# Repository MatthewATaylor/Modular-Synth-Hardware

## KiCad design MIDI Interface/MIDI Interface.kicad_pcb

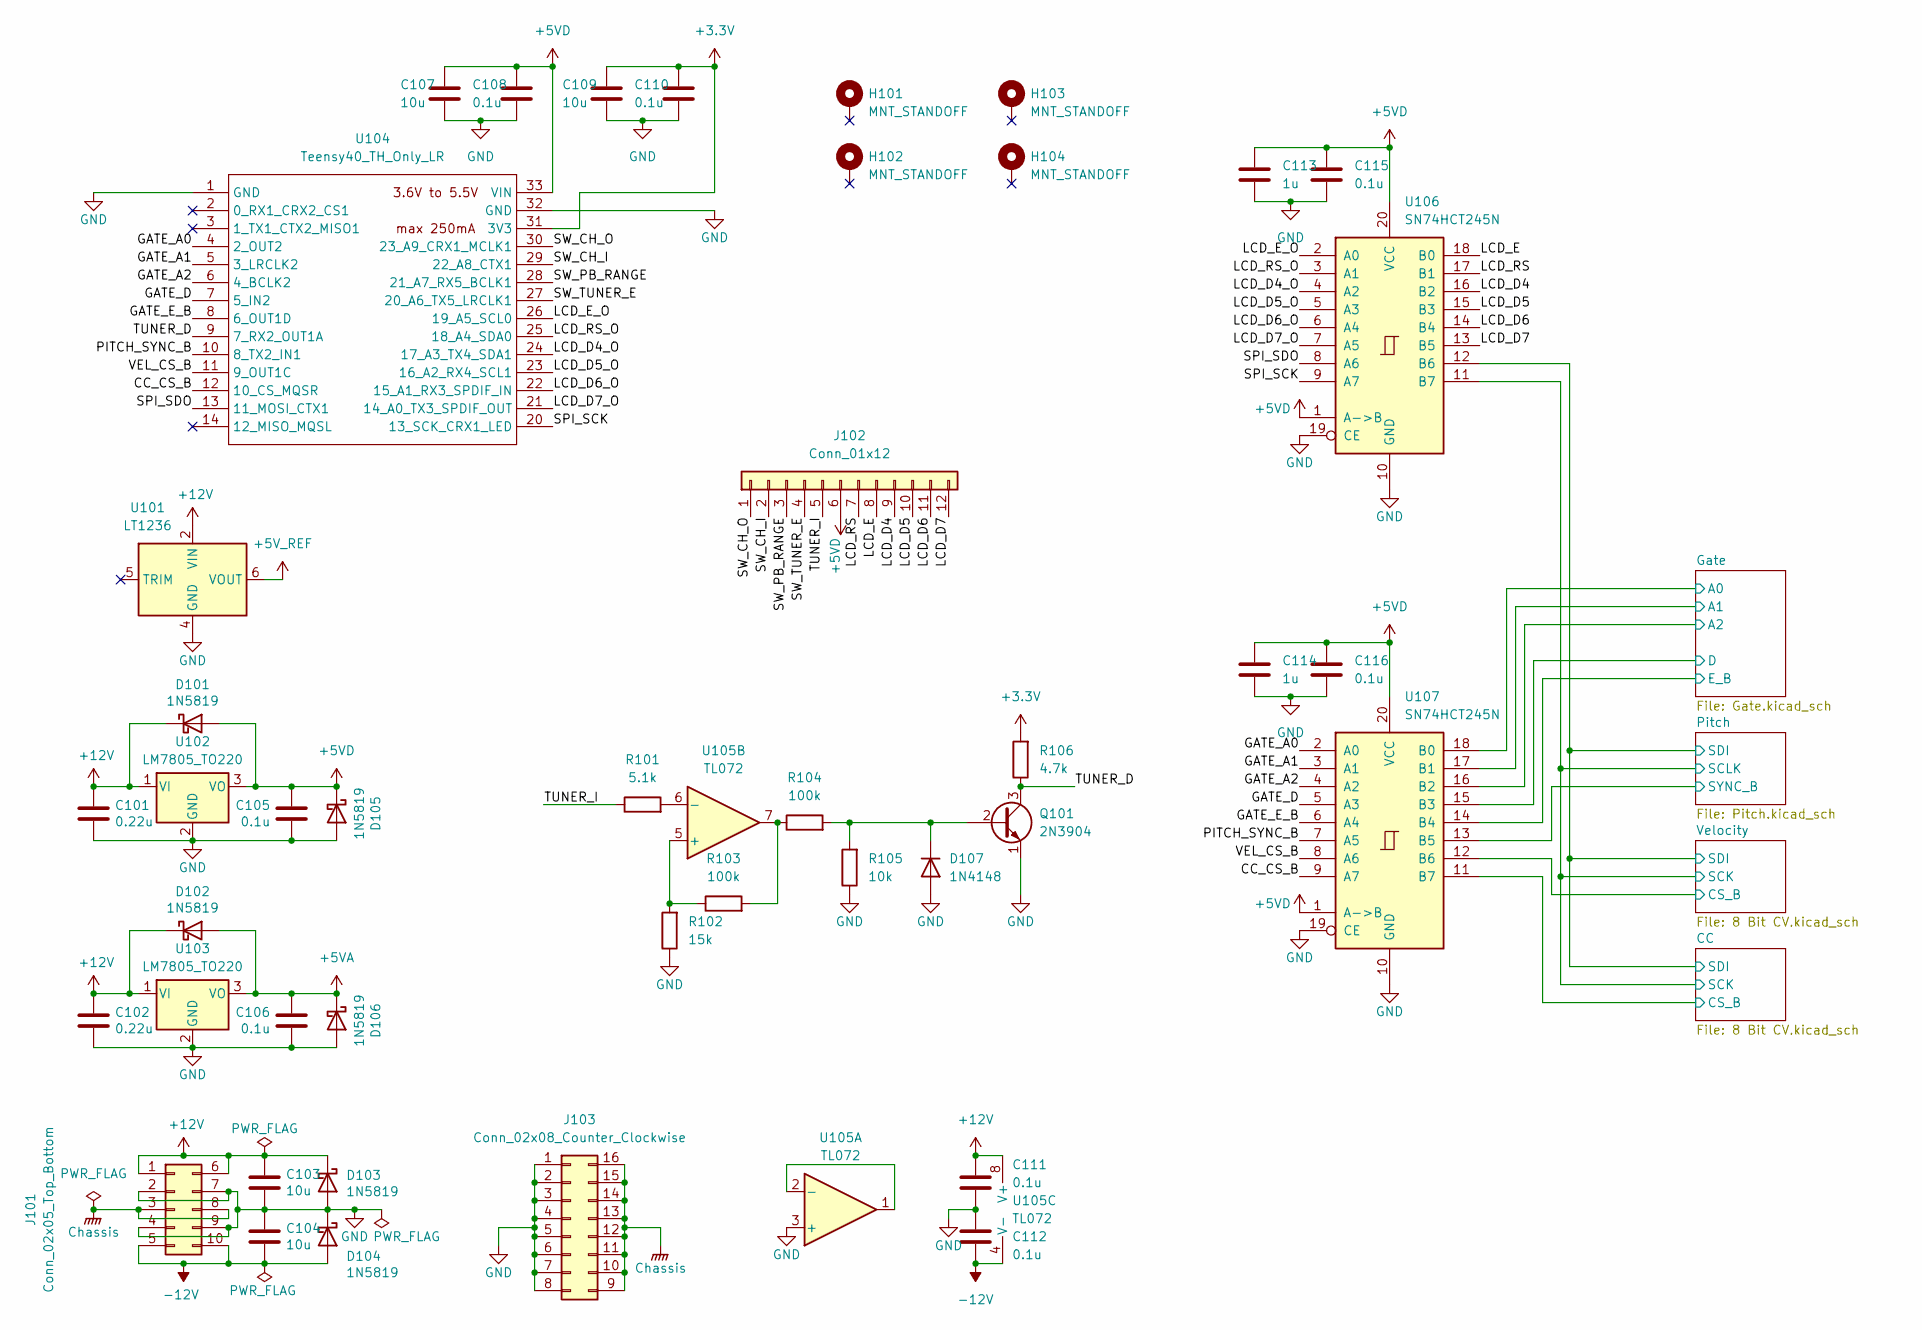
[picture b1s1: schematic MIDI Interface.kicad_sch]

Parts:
C101, C102: 0.22u; C_Disc_D5.5mm_W2.5mm_P2.50mm
C103, C104, C107, C109: 10u; C_Disc_D5.5mm_W4.0mm_P2.50mm
C105, C106, C108, C110, C111, C112, C115, C116: 0.1u; C_Disc_D5.5mm_W2.5mm_P2.50mm
C113, C114: 1u; C_Disc_D5.5mm_W4.0mm_P2.50mm
D101, D102, D103, D104, D105, D106: 1N5819; D_DO-41_SOD81_P10.16mm_Horizontal
D107: 1N4148; D_DO-35_SOD27_P7.62mm_Horizontal
H101, H102, H103, H104: MNT_STANDOFF; MountingHole_Pitch7.5mm_Drill3.4mm
J101: Conn_02x05_Top_Bottom; Molex_Mini-Fit_Jr_5566-10A_2x05_P4.20mm_Vertical
J102: Conn_01x12; PinSocket_1x12_P2.54mm_Vertical
J103: Conn_02x08_Counter_Clockwise; PinSocket_2x08_P2.54mm_Vertical
Q101: 2N3904; TO-92_HandSolder
R101: 5.1k; R_Axial_DIN0207_L6.3mm_D2.5mm_P7.62mm_Horizontal
R102: 15k; R_Axial_DIN0207_L6.3mm_D2.5mm_P7.62mm_Horizontal
R103, R104: 100k; R_Axial_DIN0207_L6.3mm_D2.5mm_P7.62mm_Horizontal
R105: 10k; R_Axial_DIN0207_L6.3mm_D2.5mm_P7.62mm_Horizontal
R106: 4.7k; R_Axial_DIN0207_L6.3mm_D2.5mm_P7.62mm_Horizontal
U101: LT1236; DIP-8_W7.62mm_Socket
U102, U103: LM7805_TO220; TO-220-3_Vertical
U104: Teensy40_TH_Only_LR
U105: TL072; DIP-8_W7.62mm_Socket
U106, U107: SN74HCT245N; DIP-20_W7.62mm_Socket

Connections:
+3.3V: C109.1, C110.1, R106.2, U104.31 (3V3)
+5VA: C106.1, D102.2 (A), D106.1 (K), U103.3 (VO); also elsewhere on the board
+5VD: C105.1, C107.1, C108.1, C113.1, C114.1, C115.1, C116.1, D101.2 (A), D105.1 (K), J102.6, U102.3 (VO), U104.33 (VIN), U106.1 (A->B), U106.20 (VCC), U107.1 (A->B), U107.20 (VCC); also elsewhere on the board
+5V_REF: U101.6 (VOUT); also elsewhere on the board
+12V: C101.1, C102.1, C103.1, C111.2, D101.1 (K), D102.1 (K), D103.1 (K), J101.1, J101.6, U101.2 (VIN), U102.1 (VI), U103.1 (VI), U105.8 (V+); also elsewhere on the board
-12V: C104.2, C112.1, D104.2 (A), J101.5, J101.10, U105.4 (V-); also elsewhere on the board
/CC/CS_B: U107.11 (B7); also elsewhere on the board
/CC/SCK: U106.11 (B7); also elsewhere on the board
/CC/SDI: U106.12 (B6); also elsewhere on the board
/CC_CS_B: U104.12 (10_CS_MQSR), U107.9 (A7)
/GATE_A0: U104.4 (2_OUT2), U107.2 (A0)
/GATE_A1: U104.5 (3_LRCLK2), U107.3 (A1)
/GATE_A2: U104.6 (4_BCLK2), U107.4 (A2)
/GATE_D: U104.7 (5_IN2), U107.5 (A3)
/GATE_E_B: U104.8 (6_OUT1D), U107.6 (A4)
/Gate/A0: U107.18 (B0); also elsewhere on the board
/Gate/A1: U107.17 (B1); also elsewhere on the board
/Gate/A2: U107.16 (B2); also elsewhere on the board
/Gate/D: U107.15 (B3); also elsewhere on the board
/Gate/E_B: U107.14 (B4); also elsewhere on the board
/LCD_D4: J102.9, U106.16 (B2)
/LCD_D4_O: U104.24 (17_A3_TX4_SDA1), U106.4 (A2)
/LCD_D5: J102.10, U106.15 (B3)
/LCD_D5_O: U104.23 (16_A2_RX4_SCL1), U106.5 (A3)
/LCD_D6: J102.11, U106.14 (B4)
/LCD_D6_O: U104.22 (15_A1_RX3_SPDIF_IN), U106.6 (A4)
/LCD_D7: J102.12, U106.13 (B5)
/LCD_D7_O: U104.21 (14_A0_TX3_SPDIF_OUT), U106.7 (A5)
/LCD_E: J102.8, U106.18 (B0)
/LCD_E_O: U104.26 (19_A5_SCL0), U106.2 (A0)
/LCD_RS: J102.7, U106.17 (B1)
/LCD_RS_O: U104.25 (18_A4_SDA0), U106.3 (A1)
/PITCH_SYNC_B: U104.10 (8_TX2_IN1), U107.7 (A5)
/Pitch/SYNC_B: U107.13 (B5); also elsewhere on the board
/SPI_SCK: U104.20 (13_SCK_CRX1_LED), U106.9 (A7)
/SPI_SDO: U104.13 (11_MOSI_CTX1), U106.8 (A6)
/SW_CH_I: J102.2, U104.29 (22_A8_CTX1)
/SW_CH_O: J102.1, U104.30 (23_A9_CRX1_MCLK1)
/SW_PB_RANGE: J102.3, U104.28 (21_A7_RX5_BCLK1)
/SW_TUNER_E: J102.4, U104.27 (20_A6_TX5_LRCLK1)
/TUNER_D: Q101.3 (C), R106.1, U104.9 (7_RX2_OUT1A)
/TUNER_I: J102.5, R101.1
/VEL_CS_B: U104.11 (9_OUT1C), U107.8 (A6)
/Velocity/CS_B: U107.12 (B6); also elsewhere on the board
Chassis: J101.3, J101.8, J103.9, J103.10, J103.11, J103.12, J103.13, J103.14, J103.15, J103.16
GND: C101.2, C102.2, C103.2, C104.1, C105.2, C106.2, C107.2, C108.2, C109.2, C110.2, C111.1, C112.2, C113.2, C114.2, C115.2, C116.2, D103.2 (A), D104.1 (K), D105.2 (A), D106.2 (A), D107.2 (A), J101.2, J101.4, J101.7, J101.9, J103.1, J103.2, J103.3, J103.4, J103.5, J103.6, J103.7, J103.8, Q101.1 (E), R102.1, R105.1, U101.4 (GND), U102.2 (GND), U103.2 (GND), U104.1 (GND), U104.32 (GND), U105.3 (+), U106.10 (GND), U106.19 (CE), U107.10 (GND), U107.19 (CE); also elsewhere on the board
unnamed: D107.1 (K), Q101.2 (B), R104.2, R105.2
unnamed: R103.2, R104.1, U105.7
unnamed: U105.1, U105.2 (-)
unnamed: R102.2, R103.1, U105.5 (+)
unnamed: R101.2, U105.6 (-)

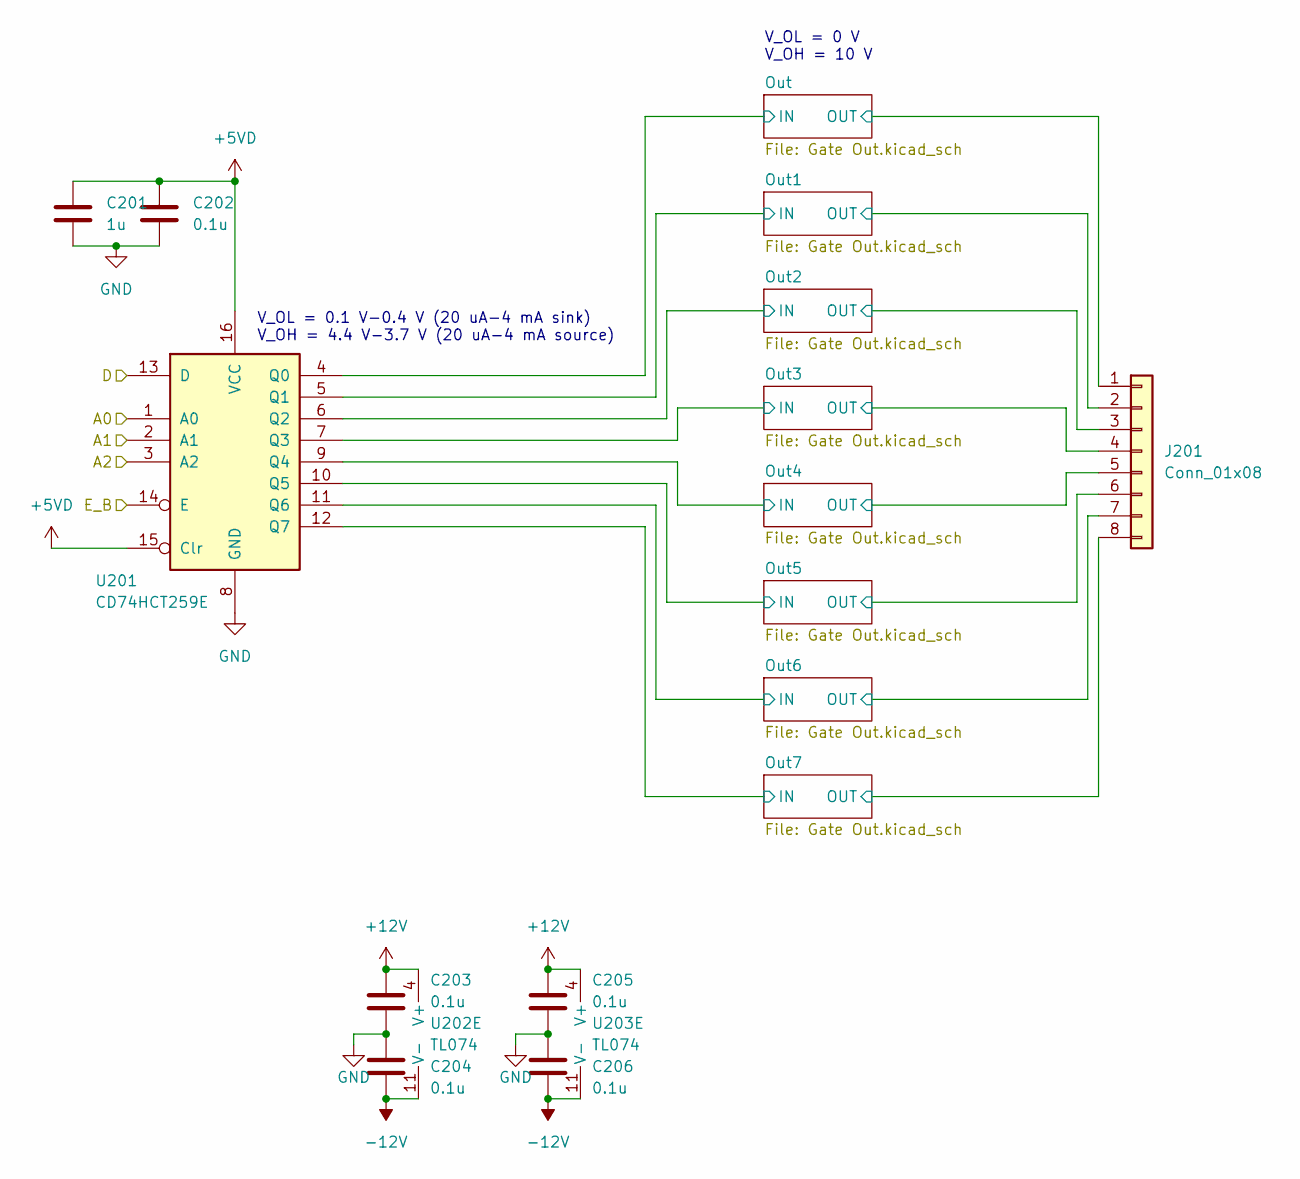
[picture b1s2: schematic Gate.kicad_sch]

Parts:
C201: 1u; C_Disc_D5.5mm_W4.0mm_P2.50mm
C202, C203, C204, C205, C206: 0.1u; C_Disc_D5.5mm_W2.5mm_P2.50mm
J201: Conn_01x08; PinHeader_1x08_P2.54mm_Vertical
U201: CD74HCT259E; DIP-16_W7.62mm_Socket
U202, U203: TL074; DIP-14_W7.62mm_Socket

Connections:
+5VD: C201.1, C202.1, U201.15 (Clr), U201.16 (VCC); also elsewhere on the board
+12V: C203.2, C205.2, U202.4 (V+), U203.4 (V+); also elsewhere on the board
-12V: C204.1, C206.1, U202.11 (V-), U203.11 (V-); also elsewhere on the board
/Gate/A0: U201.1 (A0); also elsewhere on the board
/Gate/A1: U201.2 (A1); also elsewhere on the board
/Gate/A2: U201.3 (A2); also elsewhere on the board
/Gate/D: U201.13 (D); also elsewhere on the board
/Gate/E_B: U201.14 (E); also elsewhere on the board
/Gate/Out1/IN: U201.5 (Q1); also elsewhere on the board
/Gate/Out1/OUT: J201.2; also elsewhere on the board
/Gate/Out2/IN: U201.6 (Q2); also elsewhere on the board
/Gate/Out2/OUT: J201.3; also elsewhere on the board
/Gate/Out3/IN: U201.7 (Q3); also elsewhere on the board
/Gate/Out3/OUT: J201.4; also elsewhere on the board
/Gate/Out4/IN: U201.9 (Q4); also elsewhere on the board
/Gate/Out4/OUT: J201.5; also elsewhere on the board
/Gate/Out5/IN: U201.10 (Q5); also elsewhere on the board
/Gate/Out5/OUT: J201.6; also elsewhere on the board
/Gate/Out6/IN: U201.11 (Q6); also elsewhere on the board
/Gate/Out6/OUT: J201.7; also elsewhere on the board
/Gate/Out7/IN: U201.12 (Q7); also elsewhere on the board
/Gate/Out7/OUT: J201.8; also elsewhere on the board
/Gate/Out/IN: U201.4 (Q0); also elsewhere on the board
/Gate/Out/OUT: J201.1; also elsewhere on the board
GND: C201.2, C202.2, C203.1, C204.2, C205.1, C206.2, U201.8 (GND); also elsewhere on the board
unnamed 111: U202.7; also elsewhere on the board
unnamed 112: U202.8; also elsewhere on the board
unnamed 113: U202.14; also elsewhere on the board
unnamed 115: U203.7; also elsewhere on the board
unnamed 116: U203.8; also elsewhere on the board
unnamed 117: U203.14; also elsewhere on the board
unnamed 141: U202.5 (+); also elsewhere on the board
unnamed 142: U202.6 (-); also elsewhere on the board
unnamed 143: U202.10 (+); also elsewhere on the board
unnamed 144: U202.9 (-); also elsewhere on the board
unnamed 145: U202.12 (+); also elsewhere on the board
unnamed 146: U202.13 (-); also elsewhere on the board
unnamed 149: U203.5 (+); also elsewhere on the board
unnamed 150: U203.6 (-); also elsewhere on the board
unnamed 151: U203.10 (+); also elsewhere on the board
unnamed 152: U203.9 (-); also elsewhere on the board
unnamed 153: U203.12 (+); also elsewhere on the board
unnamed 154: U203.13 (-); also elsewhere on the board

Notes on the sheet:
V_OL = 0 V V_OH = 10 V
V_OL = 0.1 V-0.4 V (20 uA-4 mA sink) V_OH = 4.4 V-3.7 V (20 uA-4 mA source)

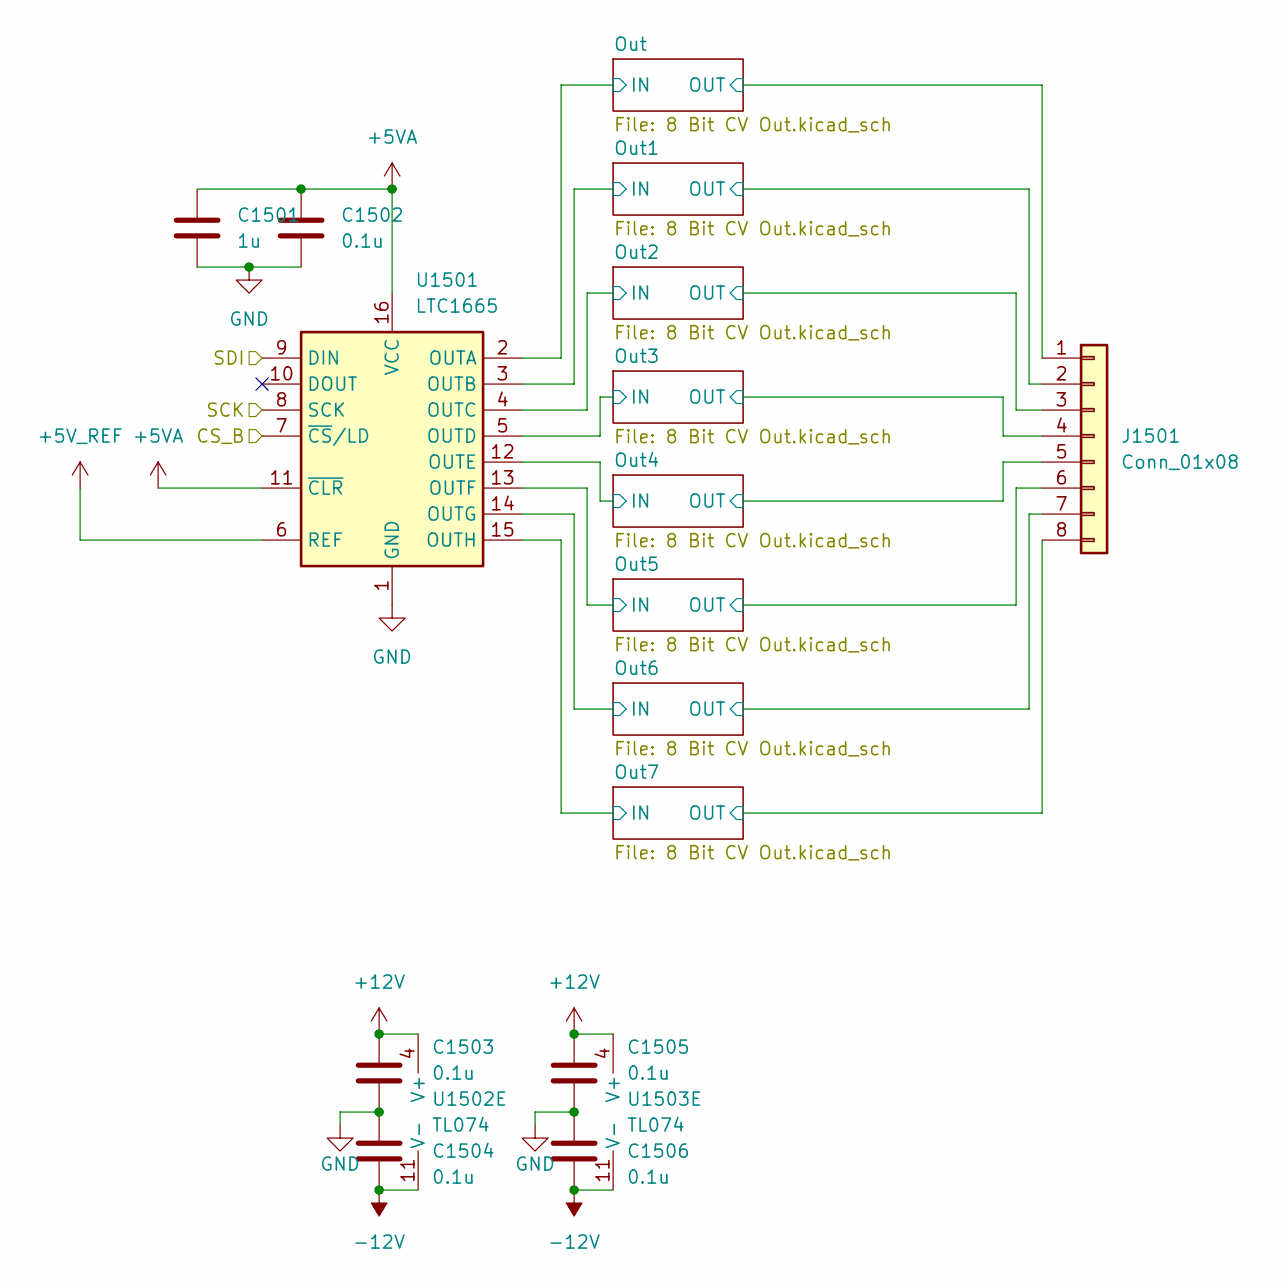
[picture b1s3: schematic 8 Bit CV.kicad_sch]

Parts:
C1501: 1u; C_Disc_D5.5mm_W4.0mm_P2.50mm
C1502, C1503, C1504, C1505, C1506: 0.1u; C_Disc_D5.5mm_W2.5mm_P2.50mm
J1501: Conn_01x08; PinHeader_1x08_P2.54mm_Vertical
U1501: LTC1665; DIP-16_W7.62mm_Socket
U1502, U1503: TL074; DIP-14_W7.62mm_Socket

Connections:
+5VA: C1501.1, C1502.1, U1501.11 (~CLR), U1501.16 (VCC); also elsewhere on the board
+5V_REF: U1501.6 (REF); also elsewhere on the board
+12V: C1503.2, C1505.2, U1502.4 (V+), U1503.4 (V+); also elsewhere on the board
-12V: C1504.1, C1506.1, U1502.11 (V-), U1503.11 (V-); also elsewhere on the board
/CC/SCK: U1501.8 (SCK); also elsewhere on the board
/CC/SDI: U1501.9 (DIN); also elsewhere on the board
/Velocity/CS_B: U1501.7 (~CS/LD); also elsewhere on the board
/Velocity/Out1/IN: U1501.3 (OUTB), U1502.5 (+)
/Velocity/Out1/OUT: J1501.2; also elsewhere on the board
/Velocity/Out2/IN: U1501.4 (OUTC), U1502.10 (+)
/Velocity/Out2/OUT: J1501.3; also elsewhere on the board
/Velocity/Out3/IN: U1501.5 (OUTD); also elsewhere on the board
/Velocity/Out3/OUT: J1501.4; also elsewhere on the board
/Velocity/Out4/IN: U1501.12 (OUTE), U1503.3 (+)
/Velocity/Out4/OUT: J1501.5; also elsewhere on the board
/Velocity/Out5/IN: U1501.13 (OUTF), U1503.5 (+)
/Velocity/Out5/OUT: J1501.6; also elsewhere on the board
/Velocity/Out6/IN: U1501.14 (OUTG), U1503.10 (+)
/Velocity/Out6/OUT: J1501.7; also elsewhere on the board
/Velocity/Out7/IN: U1501.15 (OUTH); also elsewhere on the board
/Velocity/Out7/OUT: J1501.8; also elsewhere on the board
/Velocity/Out/IN: U1501.2 (OUTA), U1502.3 (+)
/Velocity/Out/OUT: J1501.1; also elsewhere on the board
GND: C1501.2, C1502.2, C1503.1, C1504.2, C1505.1, C1506.2, U1501.1 (GND); also elsewhere on the board
unnamed 120: U1502.1; also elsewhere on the board
unnamed 121: U1502.7; also elsewhere on the board
unnamed 123: U1502.8; also elsewhere on the board
unnamed 127: U1503.1; also elsewhere on the board
unnamed 129: U1503.7; also elsewhere on the board
unnamed 131: U1503.8; also elsewhere on the board
unnamed 171: U1502.2 (-); also elsewhere on the board
unnamed 172: U1502.6 (-); also elsewhere on the board
unnamed 173: U1502.9 (-); also elsewhere on the board
unnamed 175: U1503.2 (-); also elsewhere on the board
unnamed 176: U1503.6 (-); also elsewhere on the board
unnamed 177: U1503.9 (-); also elsewhere on the board

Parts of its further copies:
C1101: 1u; C_Disc_D5.5mm_W4.0mm_P2.50mm
C1102, C1103, C1104, C1105, C1106: 0.1u; C_Disc_D5.5mm_W2.5mm_P2.50mm
J1101: Conn_01x08; PinHeader_1x08_P2.54mm_Vertical
U1101: LTC1665; DIP-16_W7.62mm_Socket
U1102, U1103: TL074; DIP-14_W7.62mm_Socket

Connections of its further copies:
+5VA: C1101.1, C1102.1, U1101.11 (~CLR), U1101.16 (VCC); also elsewhere on the board
+5V_REF: U1101.6 (REF); also elsewhere on the board
+12V: C1103.2, C1105.2, U1102.4 (V+), U1103.4 (V+); also elsewhere on the board
-12V: C1104.1, C1106.1, U1102.11 (V-), U1103.11 (V-); also elsewhere on the board
/CC/CS_B: U1101.7 (~CS/LD); also elsewhere on the board
/CC/Out1/IN: U1101.3 (OUTB), U1102.5 (+)
/CC/Out1/OUT: J1101.2; also elsewhere on the board
/CC/Out2/IN: U1101.4 (OUTC), U1102.10 (+)
/CC/Out2/OUT: J1101.3; also elsewhere on the board
/CC/Out3/IN: U1101.5 (OUTD), U1102.12 (+)
/CC/Out3/OUT: J1101.4; also elsewhere on the board
/CC/Out4/IN: U1101.12 (OUTE), U1103.3 (+)
/CC/Out4/OUT: J1101.5; also elsewhere on the board
/CC/Out5/IN: U1101.13 (OUTF), U1103.5 (+)
/CC/Out5/OUT: J1101.6; also elsewhere on the board
/CC/Out6/IN: U1101.14 (OUTG), U1103.10 (+)
/CC/Out6/OUT: J1101.7; also elsewhere on the board
/CC/Out7/IN: U1101.15 (OUTH), U1103.12 (+)
/CC/Out7/OUT: J1101.8; also elsewhere on the board
/CC/Out/IN: U1101.2 (OUTA), U1102.3 (+)
/CC/Out/OUT: J1101.1; also elsewhere on the board
/CC/SCK: U1101.8 (SCK); also elsewhere on the board
/CC/SDI: U1101.9 (DIN); also elsewhere on the board
GND: C1101.2, C1102.2, C1103.1, C1104.2, C1105.1, C1106.2, U1101.1 (GND); also elsewhere on the board
unnamed 118: U1102.1; also elsewhere on the board
unnamed 119: U1102.7; also elsewhere on the board
unnamed 122: U1102.8; also elsewhere on the board
unnamed 124: U1102.14; also elsewhere on the board
unnamed 126: U1103.1; also elsewhere on the board
unnamed 128: U1103.7; also elsewhere on the board
unnamed 130: U1103.8; also elsewhere on the board
unnamed 132: U1103.14; also elsewhere on the board
unnamed 155: U1102.2 (-); also elsewhere on the board
unnamed 156: U1102.6 (-); also elsewhere on the board
unnamed 157: U1102.9 (-); also elsewhere on the board
unnamed 158: U1102.13 (-); also elsewhere on the board
unnamed 159: U1103.2 (-); also elsewhere on the board
unnamed 160: U1103.6 (-); also elsewhere on the board
unnamed 161: U1103.9 (-); also elsewhere on the board
unnamed 162: U1103.13 (-); also elsewhere on the board

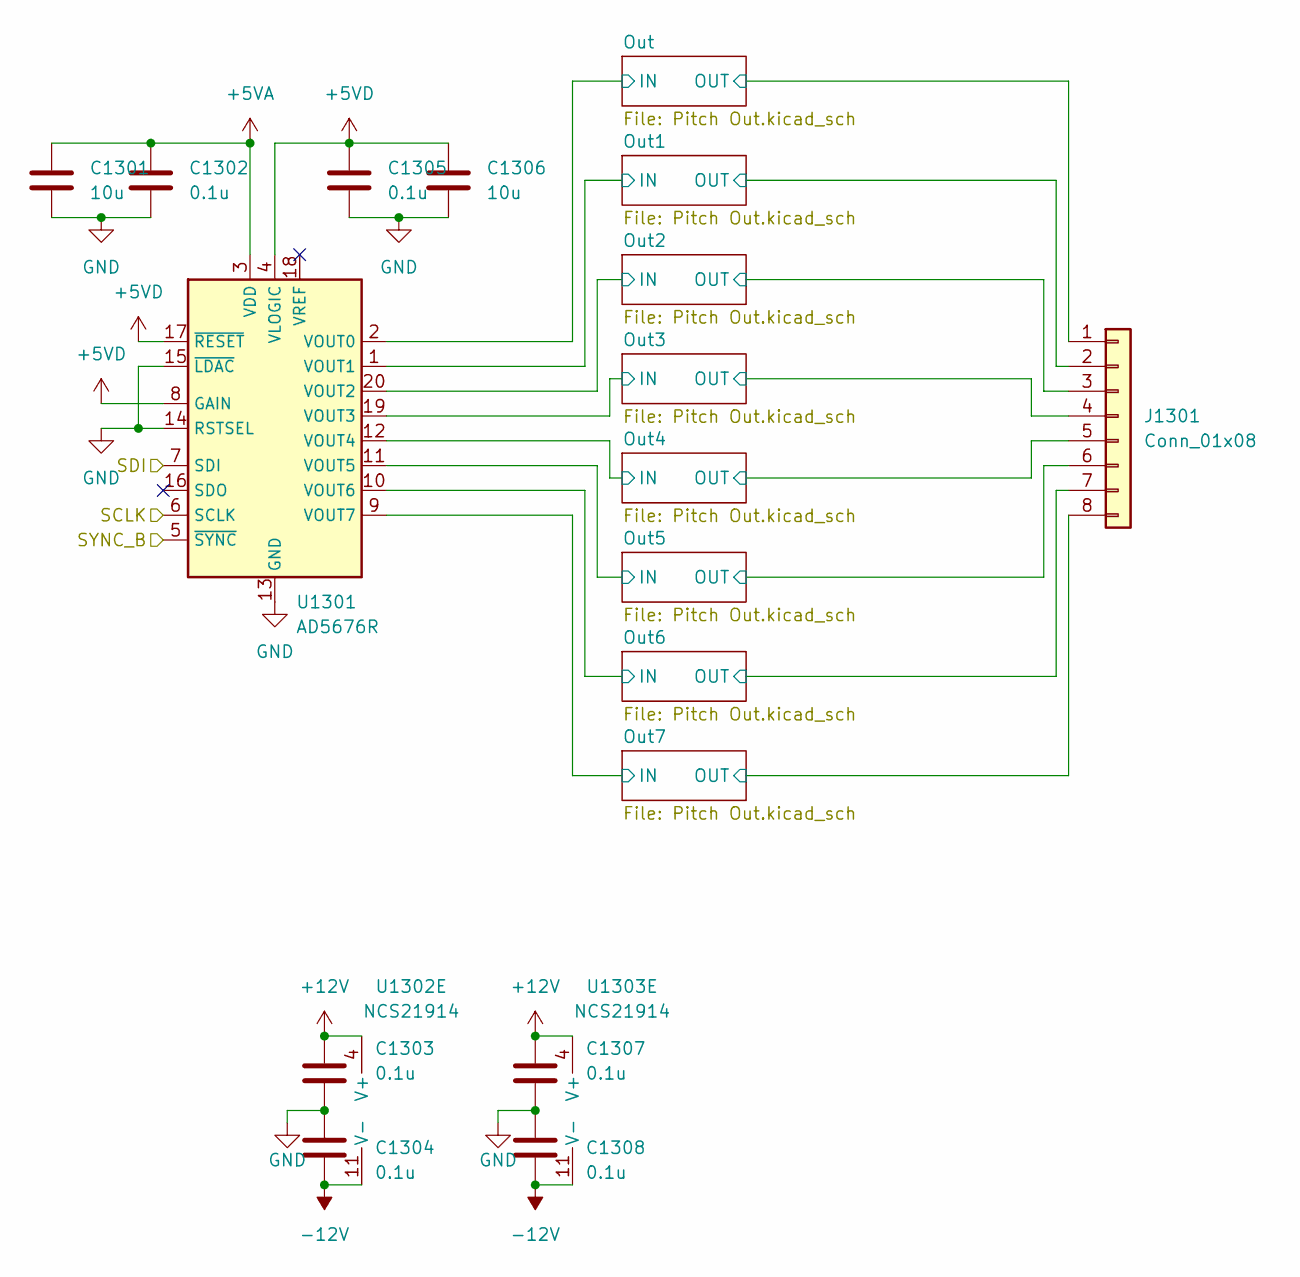
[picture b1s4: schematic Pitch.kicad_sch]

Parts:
C1301, C1306: 10u; C_Disc_D5.5mm_W4.0mm_P2.50mm
C1302, C1303, C1304, C1305, C1307, C1308: 0.1u; C_Disc_D5.5mm_W2.5mm_P2.50mm
J1301: Conn_01x08; PinHeader_1x08_P2.54mm_Vertical
U1301: AD5676R; TSSOP-20_4.4x6.5mm_P0.65mm
U1302, U1303: NCS21914; SOIC-14_3.9x8.7mm_P1.27mm

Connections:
+5VA: C1301.1, C1302.1, U1301.3 (VDD); also elsewhere on the board
+5VD: C1305.1, C1306.1, U1301.4 (VLOGIC), U1301.8 (GAIN), U1301.17 (~RESET); also elsewhere on the board
+12V: C1303.2, C1307.2, U1302.4 (V+), U1303.4 (V+); also elsewhere on the board
-12V: C1304.1, C1308.1, U1302.11 (V-), U1303.11 (V-); also elsewhere on the board
/CC/SCK: U1301.6 (SCLK); also elsewhere on the board
/CC/SDI: U1301.7 (SDI); also elsewhere on the board
/Pitch/Out1/IN: U1301.1 (VOUT1), U1302.5 (+)
/Pitch/Out1/OUT: J1301.2, U1302.7; also elsewhere on the board
/Pitch/Out2/IN: U1301.20 (VOUT2); also elsewhere on the board
/Pitch/Out2/OUT: J1301.3; also elsewhere on the board
/Pitch/Out3/IN: U1301.19 (VOUT3), U1302.12 (+)
/Pitch/Out3/OUT: J1301.4, U1302.14; also elsewhere on the board
/Pitch/Out4/IN: U1301.12 (VOUT4), U1303.3 (+)
/Pitch/Out4/OUT: J1301.5, U1303.1; also elsewhere on the board
/Pitch/Out5/IN: U1301.11 (VOUT5), U1303.5 (+)
/Pitch/Out5/OUT: J1301.6, U1303.7; also elsewhere on the board
/Pitch/Out6/IN: U1301.10 (VOUT6); also elsewhere on the board
/Pitch/Out6/OUT: J1301.7; also elsewhere on the board
/Pitch/Out7/IN: U1301.9 (VOUT7), U1303.12 (+)
/Pitch/Out7/OUT: J1301.8, U1303.14; also elsewhere on the board
/Pitch/Out/IN: U1301.2 (VOUT0), U1302.3 (+)
/Pitch/Out/OUT: J1301.1, U1302.1; also elsewhere on the board
/Pitch/SYNC_B: U1301.5 (~SYNC); also elsewhere on the board
GND: C1301.2, C1302.2, C1303.1, C1304.2, C1305.2, C1306.2, C1307.1, C1308.2, U1301.13 (GND), U1301.14 (RSTSEL), U1301.15 (~LDAC); also elsewhere on the board
unnamed 163: U1302.2 (-); also elsewhere on the board
unnamed 164: U1302.6 (-); also elsewhere on the board
unnamed 166: U1302.13 (-); also elsewhere on the board
unnamed 167: U1303.2 (-); also elsewhere on the board
unnamed 168: U1303.6 (-); also elsewhere on the board
unnamed 170: U1303.13 (-); also elsewhere on the board

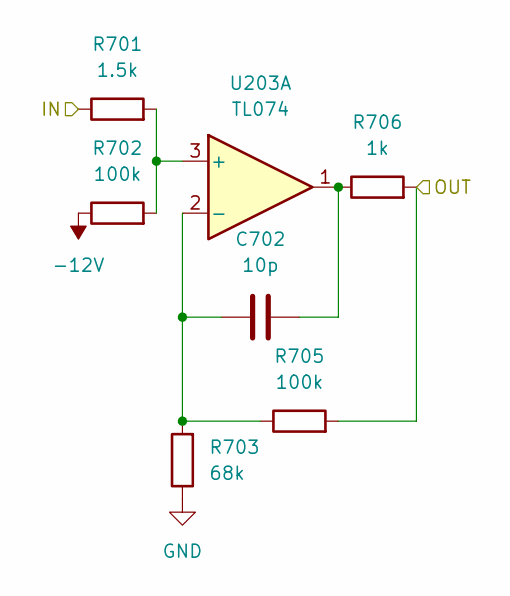
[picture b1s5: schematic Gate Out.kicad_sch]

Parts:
C702: 10p; C_Disc_D5.5mm_W2.5mm_P2.50mm
R701: 1.5k; R_Axial_DIN0207_L6.3mm_D2.5mm_P7.62mm_Horizontal
R702, R705: 100k; R_Axial_DIN0207_L6.3mm_D2.5mm_P7.62mm_Horizontal
R703: 68k; R_Axial_DIN0207_L6.3mm_D2.5mm_P7.62mm_Horizontal
R706: 1k; R_Axial_DIN0207_L6.3mm_D2.5mm_P7.62mm_Horizontal
U203: TL074; DIP-14_W7.62mm_Socket

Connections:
-12V: R702.1; also elsewhere on the board
/Gate/Out4/IN: R701.1; also elsewhere on the board
/Gate/Out4/OUT: R705.2, R706.2; also elsewhere on the board
GND: R703.1; also elsewhere on the board
unnamed: C702.2, R706.1, U203.1
unnamed 115: U203.7; also elsewhere on the board
unnamed 116: U203.8; also elsewhere on the board
unnamed 117: U203.14; also elsewhere on the board
unnamed: R701.2, R702.2, U203.3 (+)
unnamed: C702.1, R703.2, R705.1, U203.2 (-)
unnamed 149: U203.5 (+); also elsewhere on the board
unnamed 150: U203.6 (-); also elsewhere on the board
unnamed 151: U203.10 (+); also elsewhere on the board
unnamed 152: U203.9 (-); also elsewhere on the board
unnamed 153: U203.12 (+); also elsewhere on the board
unnamed 154: U203.13 (-); also elsewhere on the board

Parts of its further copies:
C302, C402, C502, C602, C802, C902, C1002: 10p; C_Disc_D5.5mm_W2.5mm_P2.50mm
R301, R401, R501, R601, R801, R901, R1001: 1.5k; R_Axial_DIN0207_L6.3mm_D2.5mm_P7.62mm_Horizontal
R302, R305, R402, R405, R502, R505, R602, R605, R802, R805, R902, R905, R1002, R1005: 100k; R_Axial_DIN0207_L6.3mm_D2.5mm_P7.62mm_Horizontal
R303, R403, R503, R603, R803, R903, R1003: 68k; R_Axial_DIN0207_L6.3mm_D2.5mm_P7.62mm_Horizontal
R306, R406, R506, R606, R806, R906, R1006: 1k; R_Axial_DIN0207_L6.3mm_D2.5mm_P7.62mm_Horizontal

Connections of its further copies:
-12V: R302.1, R402.1, R502.1, R602.1, R802.1, R902.1, R1002.1; also elsewhere on the board
/Gate/Out1/IN: R401.1; also elsewhere on the board
/Gate/Out1/OUT: R405.2, R406.2; also elsewhere on the board
/Gate/Out2/IN: R501.1; also elsewhere on the board
/Gate/Out2/OUT: R505.2, R506.2; also elsewhere on the board
/Gate/Out3/IN: R601.1; also elsewhere on the board
/Gate/Out3/OUT: R605.2, R606.2; also elsewhere on the board
/Gate/Out5/IN: R801.1; also elsewhere on the board
/Gate/Out5/OUT: R805.2, R806.2; also elsewhere on the board
/Gate/Out6/IN: R901.1; also elsewhere on the board
/Gate/Out6/OUT: R905.2, R906.2; also elsewhere on the board
/Gate/Out7/IN: R1001.1; also elsewhere on the board
/Gate/Out7/OUT: R1005.2, R1006.2; also elsewhere on the board
/Gate/Out/IN: R301.1; also elsewhere on the board
/Gate/Out/OUT: R305.2, R306.2; also elsewhere on the board
GND: R303.1, R403.1, R503.1, R603.1, R803.1, R903.1, R1003.1; also elsewhere on the board
unnamed 110: C302.2, R306.1; also elsewhere on the board
unnamed 111: C402.2, R406.1; also elsewhere on the board
unnamed 112: C502.2, R506.1; also elsewhere on the board
unnamed 113: C602.2, R606.1; also elsewhere on the board
unnamed 115: C802.2, R806.1; also elsewhere on the board
unnamed 116: C902.2, R906.1; also elsewhere on the board
unnamed 117: C1002.2, R1006.1; also elsewhere on the board
unnamed 139: R301.2, R302.2; also elsewhere on the board
unnamed 140: C302.1, R303.2, R305.1; also elsewhere on the board
unnamed 141: R401.2, R402.2; also elsewhere on the board
unnamed 142: C402.1, R403.2, R405.1; also elsewhere on the board
unnamed 143: R501.2, R502.2; also elsewhere on the board
unnamed 144: C502.1, R503.2, R505.1; also elsewhere on the board
unnamed 145: R601.2, R602.2; also elsewhere on the board
unnamed 146: C602.1, R603.2, R605.1; also elsewhere on the board
unnamed 149: R801.2, R802.2; also elsewhere on the board
unnamed 150: C802.1, R803.2, R805.1; also elsewhere on the board
unnamed 151: R901.2, R902.2; also elsewhere on the board
unnamed 152: C902.1, R903.2, R905.1; also elsewhere on the board
unnamed 153: R1001.2, R1002.2; also elsewhere on the board
unnamed 154: C1002.1, R1003.2, R1005.1; also elsewhere on the board

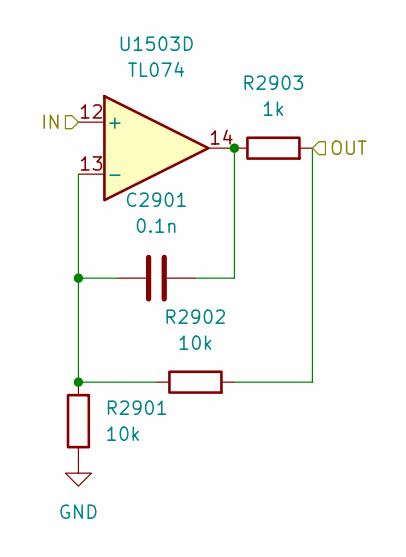
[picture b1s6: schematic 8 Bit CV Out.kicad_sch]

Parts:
C2901: 0.1n; C_Disc_D5.5mm_W2.5mm_P2.50mm
R2901, R2902: 10k; R_Axial_DIN0207_L6.3mm_D2.5mm_P7.62mm_Horizontal
R2903: 1k; R_Axial_DIN0207_L6.3mm_D2.5mm_P7.62mm_Horizontal
U1503: TL074; DIP-14_W7.62mm_Socket

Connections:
/Velocity/Out4/IN: U1503.3 (+); also elsewhere on the board
/Velocity/Out5/IN: U1503.5 (+); also elsewhere on the board
/Velocity/Out6/IN: U1503.10 (+); also elsewhere on the board
/Velocity/Out7/IN: U1503.12 (+); also elsewhere on the board
/Velocity/Out7/OUT: R2902.2, R2903.2; also elsewhere on the board
GND: R2901.1; also elsewhere on the board
unnamed 127: U1503.1; also elsewhere on the board
unnamed 129: U1503.7; also elsewhere on the board
unnamed 131: U1503.8; also elsewhere on the board
unnamed: C2901.2, R2903.1, U1503.14
unnamed 175: U1503.2 (-); also elsewhere on the board
unnamed 176: U1503.6 (-); also elsewhere on the board
unnamed 177: U1503.9 (-); also elsewhere on the board
unnamed: C2901.1, R2901.2, R2902.1, U1503.13 (-)

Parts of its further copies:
C1201, C1401, C1601, C1701, C1801, C1901, C2001, C2101, C2201, C2301, C2401, C2501, C2601, C2701, C2801: 0.1n; C_Disc_D5.5mm_W2.5mm_P2.50mm
R1201, R1202, R1401, R1402, R1601, R1602, R1701, R1702, R1801, R1802, R1901, R1902, R2001, R2002, R2101, R2102, R2201, R2202, R2301, R2302, R2401, R2402, R2501, R2502, R2601, R2602, R2701, R2702, R2801, R2802: 10k; R_Axial_DIN0207_L6.3mm_D2.5mm_P7.62mm_Horizontal
R1203, R1403, R1603, R1703, R1803, R1903, R2003, R2103, R2203, R2303, R2403, R2503, R2603, R2703, R2803: 1k; R_Axial_DIN0207_L6.3mm_D2.5mm_P7.62mm_Horizontal
U1102, U1103: TL074; DIP-14_W7.62mm_Socket

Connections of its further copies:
+12V: U1102.4 (V+), U1103.4 (V+); also elsewhere on the board
-12V: U1102.11 (V-), U1103.11 (V-); also elsewhere on the board
/CC/Out1/IN: U1102.5 (+); also elsewhere on the board
/CC/Out1/OUT: R1402.2, R1403.2; also elsewhere on the board
/CC/Out2/IN: U1102.10 (+); also elsewhere on the board
/CC/Out2/OUT: R1802.2, R1803.2; also elsewhere on the board
/CC/Out3/IN: U1102.12 (+); also elsewhere on the board
/CC/Out3/OUT: R2002.2, R2003.2; also elsewhere on the board
/CC/Out4/IN: U1103.3 (+); also elsewhere on the board
/CC/Out4/OUT: R2202.2, R2203.2; also elsewhere on the board
/CC/Out5/IN: U1103.5 (+); also elsewhere on the board
/CC/Out5/OUT: R2402.2, R2403.2; also elsewhere on the board
/CC/Out6/IN: U1103.10 (+); also elsewhere on the board
/CC/Out6/OUT: R2602.2, R2603.2; also elsewhere on the board
/CC/Out7/IN: U1103.12 (+); also elsewhere on the board
/CC/Out7/OUT: R2802.2, R2803.2; also elsewhere on the board
/CC/Out/IN: U1102.3 (+); also elsewhere on the board
/CC/Out/OUT: R1202.2, R1203.2; also elsewhere on the board
/Velocity/Out1/OUT: R1702.2, R1703.2; also elsewhere on the board
/Velocity/Out2/OUT: R1902.2, R1903.2; also elsewhere on the board
/Velocity/Out3/OUT: R2102.2, R2103.2; also elsewhere on the board
/Velocity/Out4/OUT: R2302.2, R2303.2; also elsewhere on the board
/Velocity/Out5/OUT: R2502.2, R2503.2; also elsewhere on the board
/Velocity/Out6/OUT: R2702.2, R2703.2; also elsewhere on the board
/Velocity/Out/OUT: R1602.2, R1603.2; also elsewhere on the board
GND: R1201.1, R1401.1, R1601.1, R1701.1, R1801.1, R1901.1, R2001.1, R2101.1, R2201.1, R2301.1, R2401.1, R2501.1, R2601.1, R2701.1, R2801.1; also elsewhere on the board
unnamed: C1201.2, R1203.1, U1102.1
unnamed: C1401.2, R1403.1, U1102.7
unnamed 120: C1601.2, R1603.1; also elsewhere on the board
unnamed 121: C1701.2, R1703.1; also elsewhere on the board
unnamed: C1801.2, R1803.1, U1102.8
unnamed 123: C1901.2, R1903.1; also elsewhere on the board
unnamed: C2001.2, R2003.1, U1102.14
unnamed 125: C2101.2, R2103.1; also elsewhere on the board
unnamed: C2201.2, R2203.1, U1103.1
unnamed 127: C2301.2, R2303.1; also elsewhere on the board
unnamed: C2401.2, R2403.1, U1103.7
unnamed 129: C2501.2, R2503.1; also elsewhere on the board
unnamed: C2601.2, R2603.1, U1103.8
unnamed 131: C2701.2, R2703.1; also elsewhere on the board
unnamed: C2801.2, R2803.1, U1103.14
unnamed: C1201.1, R1201.2, R1202.1, U1102.2 (-)
unnamed: C1401.1, R1401.2, R1402.1, U1102.6 (-)
unnamed: C1801.1, R1801.2, R1802.1, U1102.9 (-)
unnamed: C2001.1, R2001.2, R2002.1, U1102.13 (-)
unnamed: C2201.1, R2201.2, R2202.1, U1103.2 (-)
unnamed: C2401.1, R2401.2, R2402.1, U1103.6 (-)
unnamed: C2601.1, R2601.2, R2602.1, U1103.9 (-)
unnamed: C2801.1, R2801.2, R2802.1, U1103.13 (-)
unnamed 171: C1601.1, R1601.2, R1602.1; also elsewhere on the board
unnamed 172: C1701.1, R1701.2, R1702.1; also elsewhere on the board
unnamed 173: C1901.1, R1901.2, R1902.1; also elsewhere on the board
unnamed 174: C2101.1, R2101.2, R2102.1; also elsewhere on the board
unnamed 175: C2301.1, R2301.2, R2302.1; also elsewhere on the board
unnamed 176: C2501.1, R2501.2, R2502.1; also elsewhere on the board
unnamed 177: C2701.1, R2701.2, R2702.1; also elsewhere on the board
